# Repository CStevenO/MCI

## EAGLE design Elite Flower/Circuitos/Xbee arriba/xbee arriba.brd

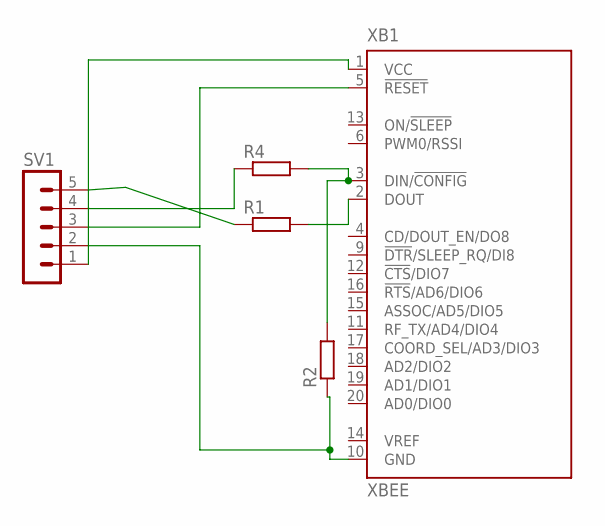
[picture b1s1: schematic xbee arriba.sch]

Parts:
R1, R2, R4: R-EU_0204/7; 0204/7
SV1: MA05-1
XB1: XBEE

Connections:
unnamed: R2.1, SV1.2, XB1.10 (GND)
unnamed: R4.1, SV1.4
unnamed: R2.2, R4.2, XB1.3 (DIN/!CONFIG)
unnamed: R1.1, SV1.5
unnamed: R1.2, XB1.2 (DOUT)
unnamed: SV1.3, XB1.5 (!RESET)
unnamed: SV1.1, XB1.1 (VCC)

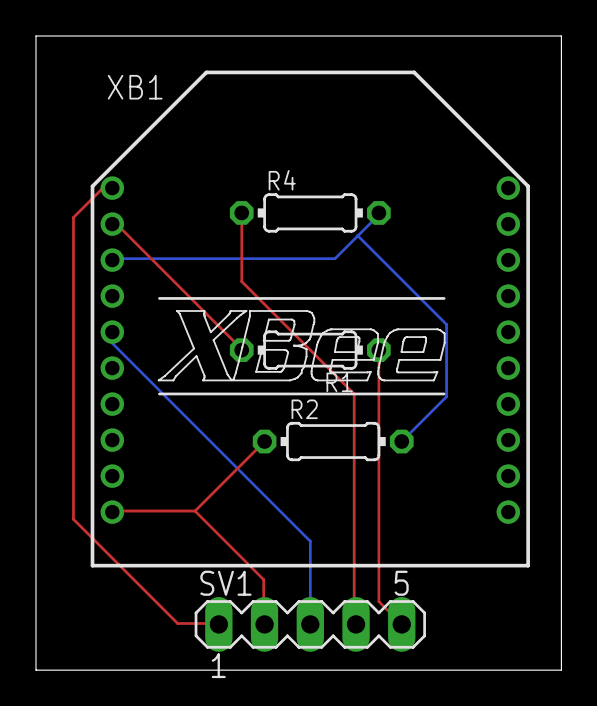
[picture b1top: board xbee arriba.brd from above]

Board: 2 copper layers, 29.2 x 35.2 mm, 5 parts (0 on the bottom side), 7 nets.

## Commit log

2020-01-13 Text
    asd
2020-01-13 Create 1
2020-01-13 Archivos Subidos
2020-01-13 Archivos Para descomprimir
2020-01-14 Prueba colocando un espacio, sin cambiar nada del codigo.
2020-01-14 Se puede programar desde arduino y se envia a Github donde lo puedo guardar realmente o crearlo como un branch
2020-01-14 nada
2020-01-18 Descompresion
2020-01-21 pruebas con el sensor de humedad separado y sensor de temperatura
2020-01-23 Circuitos Ductos
2020-02-05 Avances en la libreria XBEE
2020-02-05 SE COMENTO EL RECEIVEPACKET
2020-02-05 no se que hice
2020-02-05 Arreglos
2020-02-08 Hola
2020-02-08 Ya compila, pero toca verificar por que no funciona
2020-02-11 Arreglos para que funcione
2020-02-15 arreglando la recepcion de informacion...
2020-02-18 ya recibe datos pero sí se cambia de tamaño el mensaje se bloquea :(
2020-02-19 Ya funciona la recepcion de informacion (pero la memoria dinamica no se esta borrando correctamente, así que quedo deshabilitada) y el estado de envio, falta revisar la tranmision de informacion
2020-02-21 ¿Ya se podrán enviar datos? (Falta prueba)
2020-02-21 tratando de arreglar pero no funciono
2020-02-27 XBEE libreria y pruebas varias, pero faltan más
2020-02-28 prueba para ductos (sensor de presion)
2020-03-10 eespac i i o
2020-03-10 dffyfyt
2020-03-10 cambios
2020-03-18 prueba
2020-03-19 ductos
2020-03-19 Muestra por serial
2020-03-25 Sublimacion
2020-03-25 varias sublimaciones al día
2020-03-25 programa de sublimacion para los invernaderos con XBEE
2020-04-29 no sé
2020-05-13 xbee
2020-05-13 Baquela XBEE
2020-06-02 no se
2020-06-17 toca probarlo
2020-06-17 niksd
2020-06-19 funcionalidades no probadas porque no tengo conexion con la red
2020-06-20 hora
2020-06-20 hlsvdjka
2020-06-22 asdfa
2020-06-23 Avances Covid
2020-06-23 esp32 funciona
2020-06-25 sensor de temperatura IR
2020-06-26 covid
2020-06-27 tarjeta
2020-06-27 datos de fabricacion
2020-06-30 funciona el barcode :D
2020-07-01 gerbers
2020-07-01 pruebas
2020-07-06 PCB con Pantalla SPI
2020-07-06 arreglos en el codigo
2020-07-07 baquelas
2020-07-08 quien sabe
2020-07-09 yhghjg
2020-07-10 mjyg,jgj
2020-07-11 jyjhgj
2020-07-11 ZDASD
2020-07-11 jfjhfhj
2020-07-13 jbasda
2020-07-16 zxccz
2020-07-16 fsdasda
2020-07-16 sfdfdb
2020-07-21 erqweqw
2020-07-21 sadasda
2020-07-22 sadasd
2020-07-22 asdasda
2020-07-22 jasdbasbdjab
2020-08-04 arreglos?
2020-08-27 mejoras totales
    no me acuerdo cuales fueron los arreglos que hice
2020-09-02 arreglos en invernaderos
2020-09-03 Avances sustanciales, falta arreglar el codigo deñ arduino para que reciba datos de configuracion,hora, y pueda enviar datos
2020-09-07 arreglos varios
2020-09-08 arreglos en los horarios para activarse por horarios programados
2020-09-09 No me acuerdo que fue lo que hice
2020-09-14 asdas
2020-09-14 jgcjgvg
2020-09-15 arreglos faltan pruebas de control de dispostivos
2020-09-18 arreglos generales
2020-09-23 arreglos varios
    arreglos variados
2020-09-30 Flujo
    Flujo de Node-red
